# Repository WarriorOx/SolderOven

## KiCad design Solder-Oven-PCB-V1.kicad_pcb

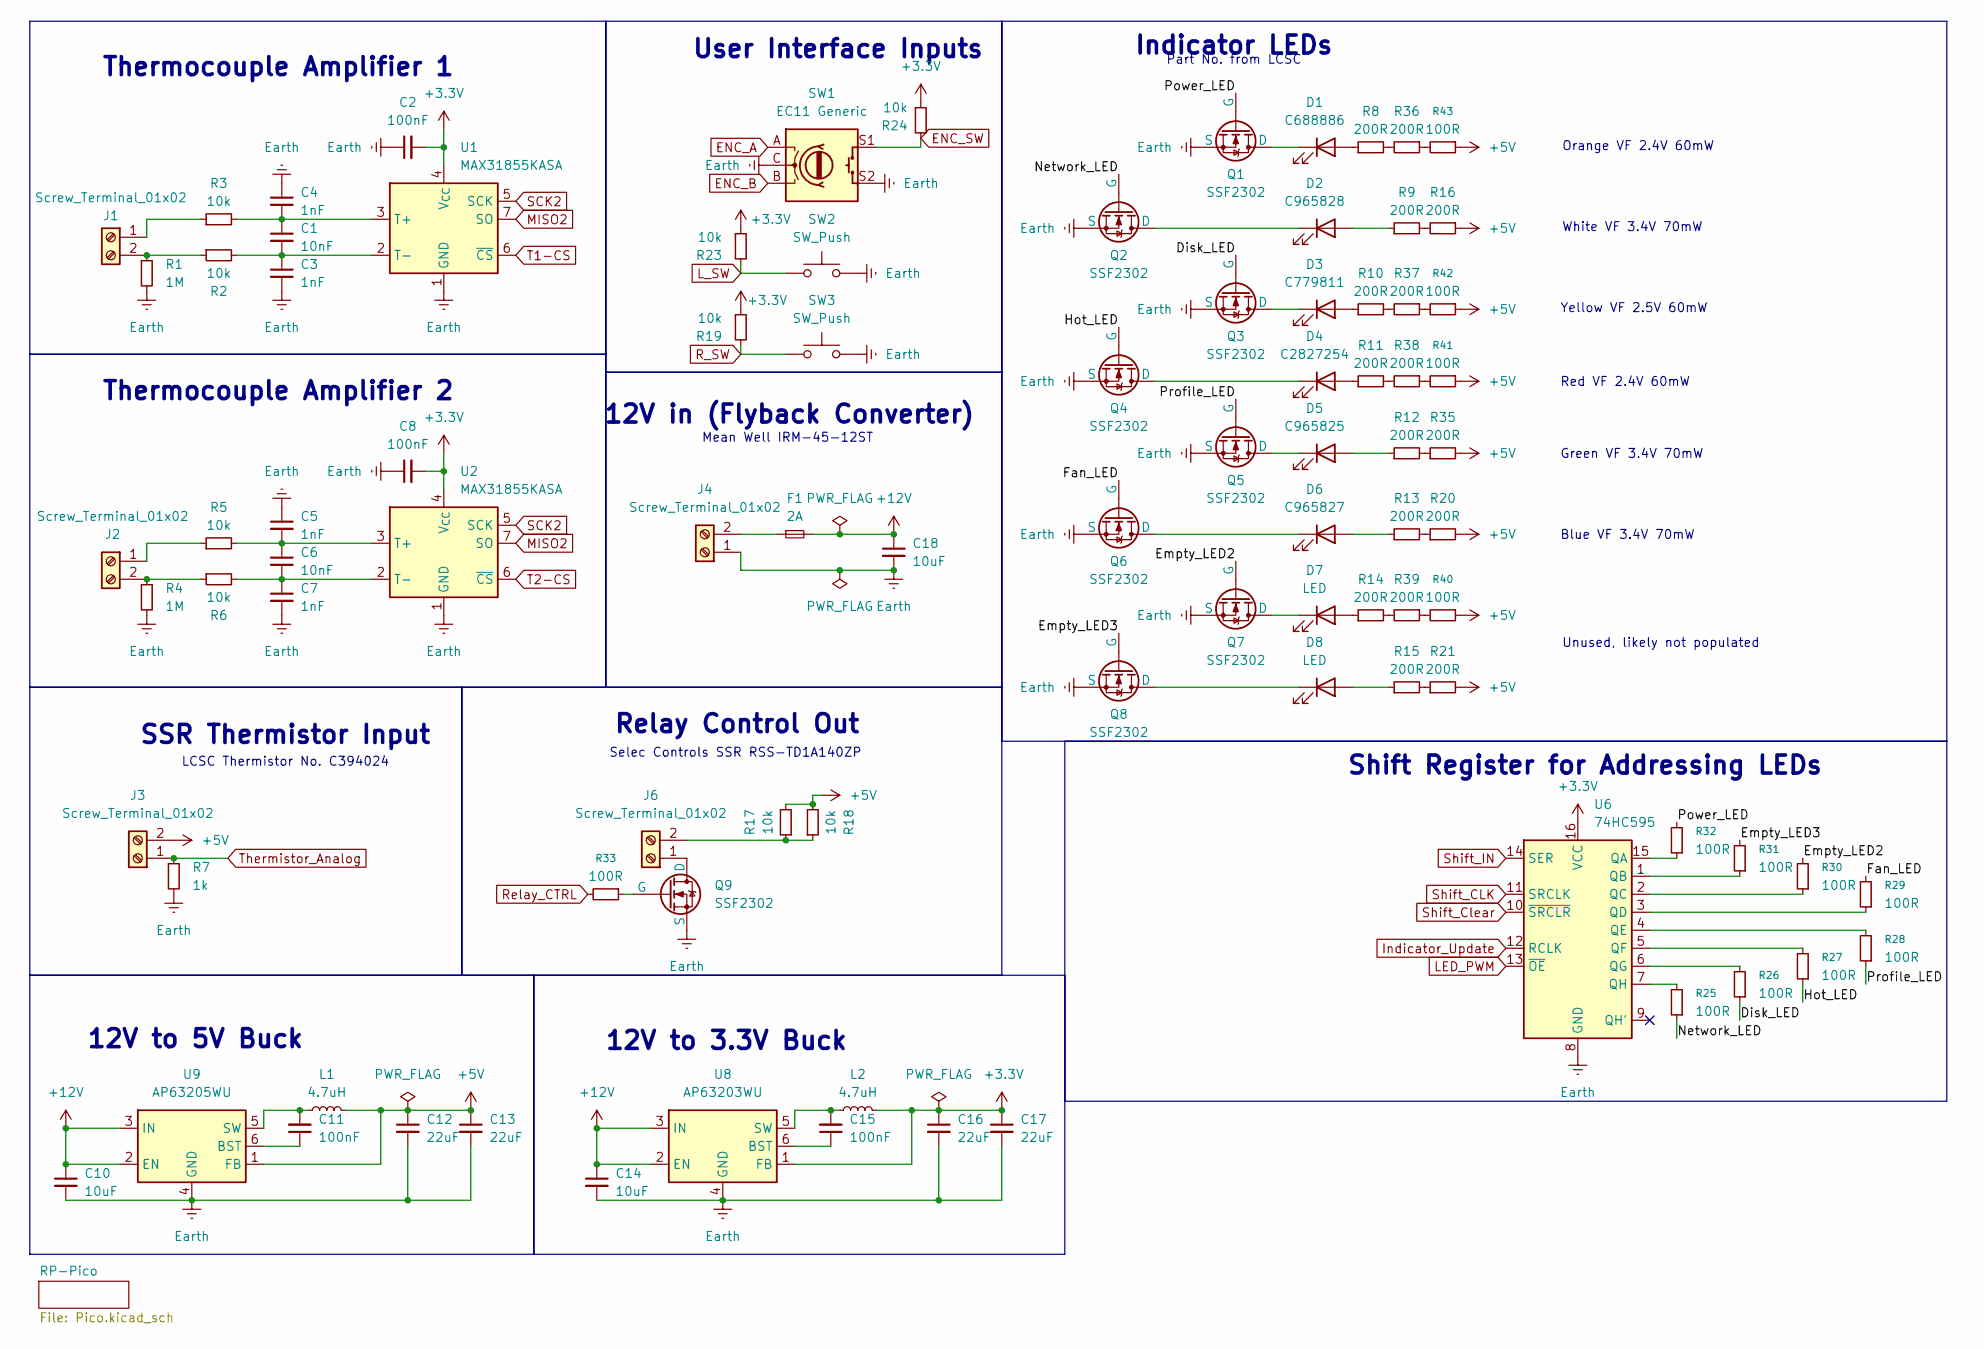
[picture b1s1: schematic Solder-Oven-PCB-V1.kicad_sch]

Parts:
C1, C6: 10nF; C_0603_1608Metric_Pad1.08x0.95mm_HandSolder
C2, C8, C11, C15: 100nF; C_0603_1608Metric_Pad1.08x0.95mm_HandSolder
C3, C4, C5, C7: 1nF; C_0603_1608Metric_Pad1.08x0.95mm_HandSolder
C10, C14, C18: 10uF; C_0603_1608Metric_Pad1.08x0.95mm_HandSolder
C12, C13, C16, C17: 22uF; C_0603_1608Metric_Pad1.08x0.95mm_HandSolder
D1: C688886; LED_1206_3216Metric_Pad1.42x1.75mm_HandSolder
D2: C965828; LED_1206_3216Metric_Pad1.42x1.75mm_HandSolder
D3: C779811; LED_1206_3216Metric_Pad1.42x1.75mm_HandSolder
D4: C2827254; LED_1206_3216Metric_Pad1.42x1.75mm_HandSolder
D5: C965825; LED_1206_3216Metric_Pad1.42x1.75mm_HandSolder
D6: C965827; LED_1206_3216Metric_Pad1.42x1.75mm_HandSolder
D7, D8: LED; LED_1206_3216Metric_Pad1.42x1.75mm_HandSolder
F1: 2A; Fuse_1812_4532Metric_Pad1.30x3.40mm_HandSolder
J1, J2, J3, J4, J6: Screw_Terminal_01x02; 1x2 5.08mm Screw Terminal
L1, L2: 4.7uH; LCSCC22463808
Q1, Q2, Q3, Q4, Q5, Q6, Q7, Q8, Q9: SSF2302; SOT-23-3
R1, R4: 1M; R_0603_1608Metric_Pad0.98x0.95mm_HandSolder
R2, R3, R5, R6, R17, R18, R19, R23, R24: 10k; R_0603_1608Metric_Pad0.98x0.95mm_HandSolder
R7: 1k; R_0603_1608Metric_Pad0.98x0.95mm_HandSolder
R8, R9, R10, R11, R12, R13, R14, R15, R16, R20, R21, R35, R36, R37, R38, R39: 200R; R_0603_1608Metric_Pad0.98x0.95mm_HandSolder
R25, R26, R27, R28, R29, R30, R31, R32, R33, R40, R41, R42, R43: 100R; R_0603_1608Metric_Pad0.98x0.95mm_HandSolder
SW1: EC11 Generic; RotaryEncoder_Alps_EC11E-Switch_Vertical_H20mm
SW2, SW3: SW_Push; MXOnly-1U-NoLED
U1, U2: MAX31855KASA; SOIC-8_3.9x4.9mm_P1.27mm
U6: 74HC595; SOP-16_3.9x9.9mm_P1.27mm
U8: AP63203WU; TSOT-23-6
U9: AP63205WU; TSOT-23-6

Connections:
+3.3V: C2.2, C8.2, C16.1, C17.1, L2.2, R19.1, R23.1, R24.1, U1.4 (V_{CC}), U2.4 (V_{CC}), U6.16 (VCC), U8.1 (FB); also elsewhere on the board
+5V: C12.1, C13.1, J3.2, L1.2, R16.1, R17.2, R18.2, R20.2, R21.2, R35.2, R40.1, R41.1, R42.1, R43.1, U9.1 (FB); also elsewhere on the board
+12V: C10.1, C14.1, C18.1, F1.2, U8.2 (EN), U8.3 (IN), U9.2 (EN), U9.3 (IN); also elsewhere on the board
/Disk_LED: Q3.2 (G), R26.1
/Empty_LED2: Q7.2 (G), R30.2
/Empty_LED3: Q8.2 (G), R31.2
/Fan_LED: Q6.2 (G), R29.2
/Hot_LED: Q4.2 (G), R27.1
/Network_LED: Q2.2 (G), R25.1
/Power_LED: Q1.2 (G), R32.2
/Profile_LED: Q5.2 (G), R28.1
ENC_A: SW1.A; also elsewhere on the board
ENC_B: SW1.B; also elsewhere on the board
ENC_SW: R24.2, SW1.S1; also elsewhere on the board
Earth: C2.1, C3.2, C4.1, C5.1, C7.2, C8.1, C10.2, C12.2, C13.2, C14.2, C16.2, C17.2, C18.2, J4.1, Q1.3 (S), Q2.3 (S), Q3.3 (S), Q4.3 (S), Q5.3 (S), Q6.3 (S), Q7.3 (S), Q8.3 (S), Q9.3 (S), R1.2, R4.2, R7.2, SW1.C, SW1.S2, SW2.2, SW3.2, U1.1 (GND), U2.1 (GND), U6.8 (GND), U8.4 (GND), U9.4 (GND); also elsewhere on the board
Indicator_Update: U6.12 (RCLK); also elsewhere on the board
LED_PWM: U6.13 (~OE); also elsewhere on the board
L_SW: R23.2, SW2.1; also elsewhere on the board
MISO2: U1.7 (SO), U2.7 (SO); also elsewhere on the board
unnamed: D1.2 (A), R8.1
unnamed: D1.1 (K), Q1.1 (D)
unnamed: D2.2 (A), R9.1
unnamed: D2.1 (K), Q2.1 (D)
unnamed: D3.2 (A), R10.1
unnamed: D3.1 (K), Q3.1 (D)
unnamed: D4.2 (A), R11.1
unnamed: D4.1 (K), Q4.1 (D)
unnamed: D5.2 (A), R12.1
unnamed: D5.1 (K), Q5.1 (D)
unnamed: D6.2 (A), R13.1
unnamed: D6.1 (K), Q6.1 (D)
unnamed: D7.2 (A), R14.1
unnamed: D7.1 (K), Q7.1 (D)
unnamed: D8.2 (A), R15.1
unnamed: D8.1 (K), Q8.1 (D)
unnamed: J1.1, R3.1
unnamed: J1.2, R1.1, R2.1
unnamed: J2.1, R5.1
unnamed: J2.2, R4.1, R6.1
unnamed: F1.1, J4.2
unnamed: J6.1, Q9.1 (D)
unnamed: J6.2, R17.1, R18.1
unnamed: Q9.2 (G), R33.1
unnamed: R10.2, R37.2
unnamed: R11.2, R38.2
unnamed: R12.2, R35.1
unnamed: R13.2, R20.1
unnamed: R14.2, R39.2
unnamed: R15.2, R21.1
unnamed: R9.2, R16.2
unnamed: R36.1, R43.2
unnamed: R8.2, R36.2
unnamed: R37.1, R42.2
unnamed: R38.1, R41.2
unnamed: R39.1, R40.2
unnamed: C1.1, C4.2, R3.2, U1.3 (T+)
unnamed: C1.2, C3.1, R2.2, U1.2 (T-)
unnamed: C5.2, C6.1, R5.2, U2.3 (T+)
unnamed: C6.2, C7.1, R6.2, U2.2 (T-)
unnamed: R32.1, U6.15 (QA)
unnamed: R31.1, U6.1 (QB)
unnamed: R30.1, U6.2 (QC)
unnamed: R29.1, U6.3 (QD)
unnamed: R28.2, U6.4 (QE)
unnamed: R27.2, U6.5 (QF)
unnamed: R26.2, U6.6 (QG)
unnamed: R25.2, U6.7 (QH)
unnamed: C15.1, U8.6 (BST)
unnamed: C15.2, L2.1, U8.5 (SW)
unnamed: C11.1, U9.6 (BST)
unnamed: C11.2, L1.1, U9.5 (SW)
R_SW: R19.2, SW3.1; also elsewhere on the board
Relay_CTRL: R33.2; also elsewhere on the board
SCK2: U1.5 (SCK), U2.5 (SCK); also elsewhere on the board
Shift_CLK: U6.11 (SRCLK); also elsewhere on the board
Shift_Clear: U6.10 (~SRCLR); also elsewhere on the board
Shift_IN: U6.14 (SER); also elsewhere on the board
T1-CS: U1.6 (~CS); also elsewhere on the board
T2-CS: U2.6 (~CS); also elsewhere on the board
Thermistor_Analog: J3.1, R7.1; also elsewhere on the board

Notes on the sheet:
Thermocouple Amplifier 1
Yellow VF 2.5V 60mW
Orange VF 2.4V 60mW
Part No. from LCSC
User Interface Inputs
White VF 3.4V 70mW
Thermocouple Amplifier 2
Mean Well IRM-45-12ST
12V to 3.3V Buck
Blue VF 3.4V 70mW
LCSC Thermistor No. C394024
Green VF 3.4V 70mW
Shift Register for Addressing LEDs
SSR Thermistor Input
Red VF 2.4V 60mW
Unused, likely not populated
12V to 5V Buck
Relay Control Out
Indicator LEDs
12V in (Flyback Converter)
Selec Controls SSR RSS-TD1A140ZP

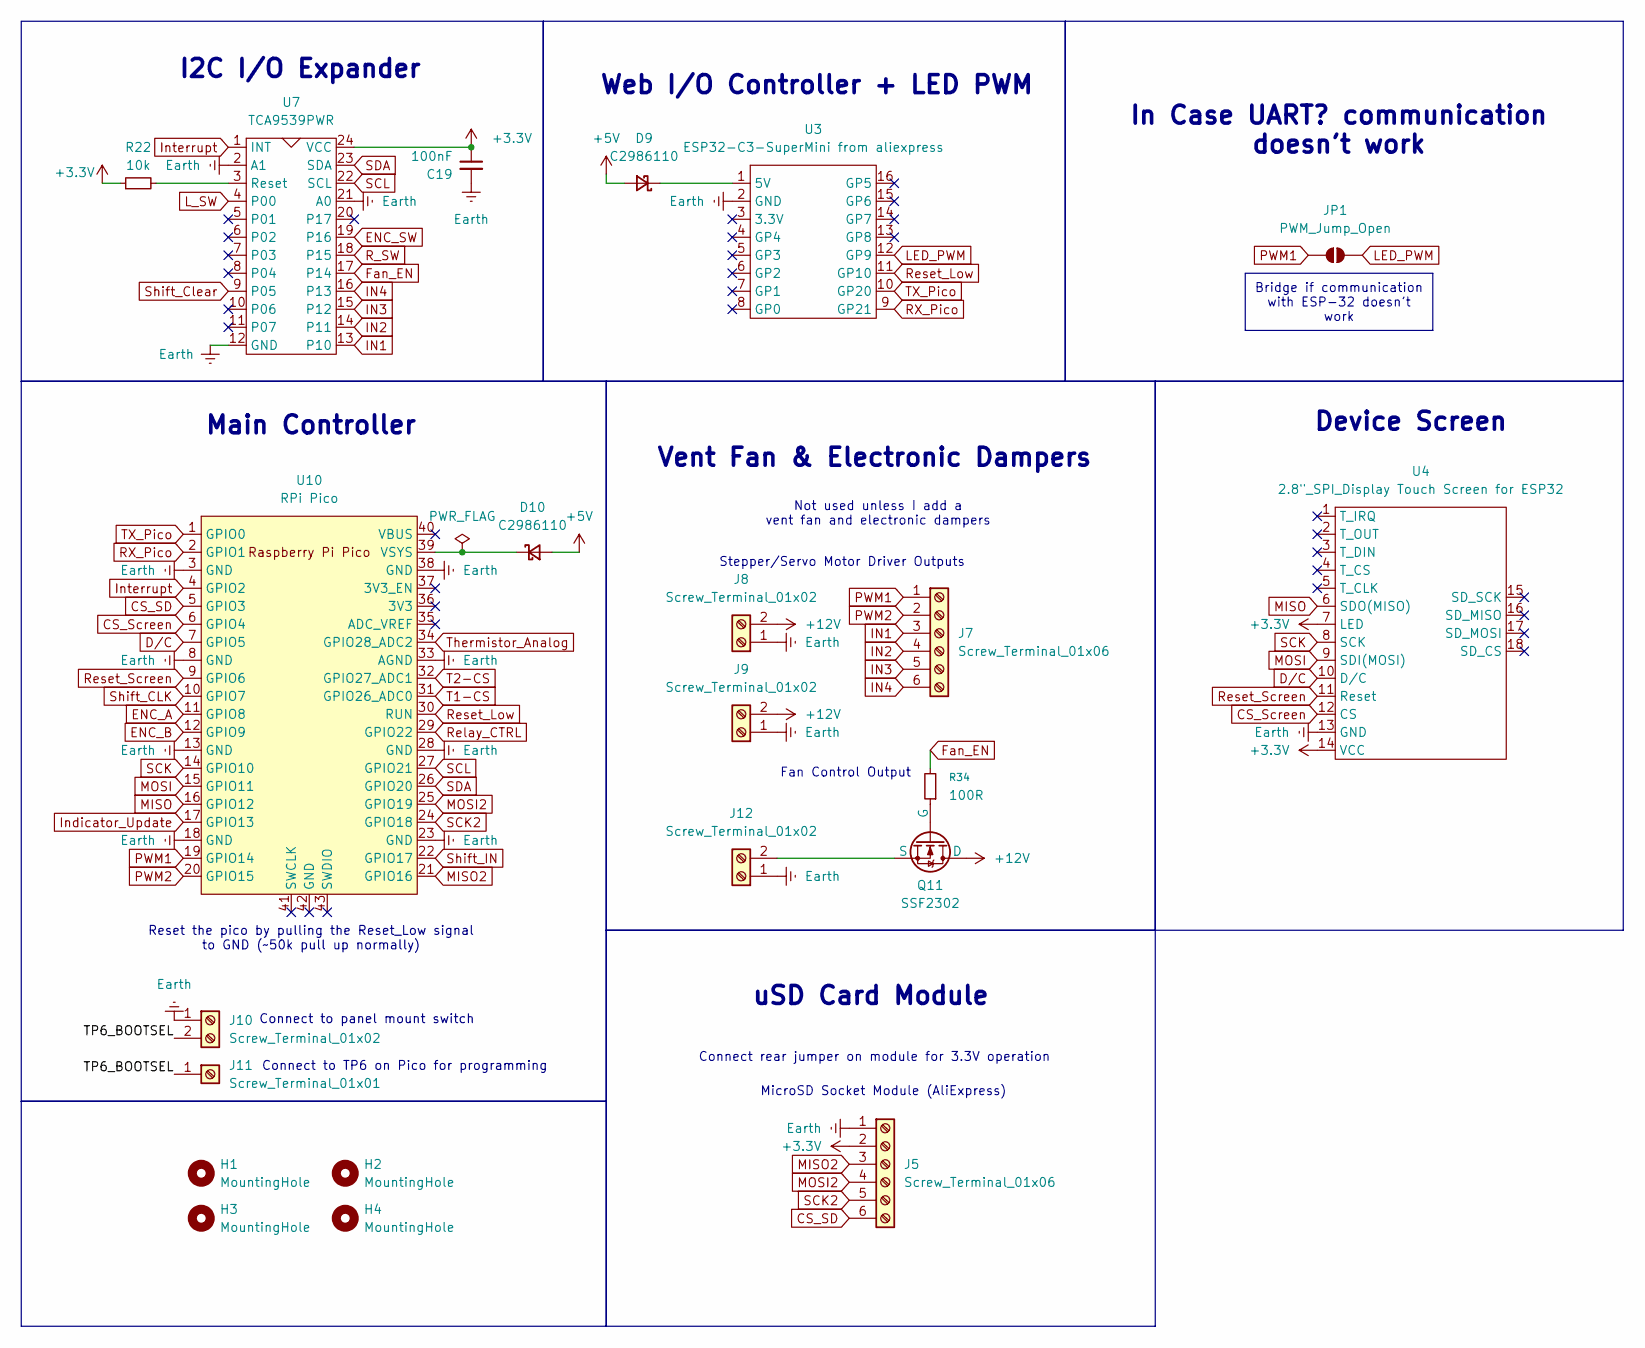
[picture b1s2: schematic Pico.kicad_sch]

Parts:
C19: 100nF; C_0603_1608Metric_Pad1.08x0.95mm_HandSolder
D9, D10: C2986110; D_SMA_Handsoldering
H1, H2, H3, H4: MountingHole; MountingHole_4mm_Pad
J5, J7: Screw_Terminal_01x06; 1x6 2.54mm Screw Terminal
J8, J9, J10, J12: Screw_Terminal_01x02; 1x2 5.08mm Screw Terminal
J11: Screw_Terminal_01x01; PinSocket_1x01_P2.54mm_Vertical
JP1: PWM_Jump_Open; SolderJumper-2_P1.3mm_Open_TrianglePad1.0x1.5mm
Q11: SSF2302; SOT-23-3
R22: 10k; R_0603_1608Metric_Pad0.98x0.95mm_HandSolder
R34: 100R; R_0603_1608Metric_Pad0.98x0.95mm_HandSolder
U3: ESP32-C3-SuperMini from aliexpress; ESP32-C3_SUPERMINI
U4: 2.8"_SPI_Display Touch Screen for ESP32; 2.8in TFT Display
U7: TCA9539PWR; TSSOP-24_4.4x7.8mm_P0.65mm
U10: RPi Pico; RPi_Pico_SMD_TH

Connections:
+3.3V: C19.1, J5.2, R22.1, U4.7 (LED), U4.14 (VCC), U7.24 (VCC); also elsewhere on the board
+5V: D9.2 (A), D10.2 (A); also elsewhere on the board
+12V: J8.2, J9.2, Q11.1 (D); also elsewhere on the board
/RP-Pico/TP6_BOOTSEL: J10.2, J11.1
CS_SD: J5.6, U10.5 (GPIO3)
CS_Screen: U4.12 (CS), U10.6 (GPIO4)
D/C: U4.10 (D/C), U10.7 (GPIO5)
ENC_A: U10.11 (GPIO8); also elsewhere on the board
ENC_B: U10.12 (GPIO9); also elsewhere on the board
ENC_SW: U7.19 (P16); also elsewhere on the board
Earth: C19.2, J5.1, J8.1, J9.1, J10.1, J12.1, U3.2 (GND), U4.13 (GND), U7.2 (A1), U7.12 (GND), U7.21 (A0), U10.3 (GND), U10.8 (GND), U10.13 (GND), U10.18 (GND), U10.23 (GND), U10.28 (GND), U10.33 (AGND), U10.38 (GND); also elsewhere on the board
Fan_EN: R34.2, U7.17 (P14)
IN1: J7.3, U7.13 (P10)
IN2: J7.4, U7.14 (P11)
IN3: J7.5, U7.15 (P12)
IN4: J7.6, U7.16 (P13)
Indicator_Update: U10.17 (GPIO13); also elsewhere on the board
Interrupt: U7.1 (INT), U10.4 (GPIO2)
LED_PWM: JP1.2 (B), U3.12 (GP9); also elsewhere on the board
L_SW: U7.4 (P00); also elsewhere on the board
MISO: U4.6 (SDO(MISO)), U10.16 (GPIO12)
MISO2: J5.3, U10.21 (GPIO16); also elsewhere on the board
MOSI: U4.9 (SDI(MOSI)), U10.15 (GPIO11)
MOSI2: J5.4, U10.25 (GPIO19)
unnamed: D9.1 (K), U3.1 (5V)
unnamed: D10.1 (K), U10.39 (VSYS)
unnamed: J12.2, Q11.3 (S)
unnamed: Q11.2 (G), R34.1
unnamed: R22.2, U7.3 (Reset)
PWM1: J7.1, JP1.1 (A), U10.19 (GPIO14)
PWM2: J7.2, U10.20 (GPIO15)
RX_Pico: U3.9 (GP21), U10.2 (GPIO1)
R_SW: U7.18 (P15); also elsewhere on the board
Relay_CTRL: U10.29 (GPIO22); also elsewhere on the board
Reset_Low: U3.11 (GP10), U10.30 (RUN)
Reset_Screen: U4.11 (Reset), U10.9 (GPIO6)
SCK: U4.8 (SCK), U10.14 (GPIO10)
SCK2: J5.5, U10.24 (GPIO18); also elsewhere on the board
SCL: U7.22 (SCL), U10.27 (GPIO21)
SDA: U7.23 (SDA), U10.26 (GPIO20)
Shift_CLK: U10.10 (GPIO7); also elsewhere on the board
Shift_Clear: U7.9 (P05); also elsewhere on the board
Shift_IN: U10.22 (GPIO17); also elsewhere on the board
T1-CS: U10.31 (GPIO26_ADC0); also elsewhere on the board
T2-CS: U10.32 (GPIO27_ADC1); also elsewhere on the board
TX_Pico: U3.10 (GP20), U10.1 (GPIO0)
Thermistor_Analog: U10.34 (GPIO28_ADC2); also elsewhere on the board

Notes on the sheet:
Main Controller
I2C I/O Expander
Connect rear jumper on module for 3.3V operation
Device Screen
uSD Card Module
MicroSD Socket Module (AliExpress)
In Case UART? communication doesn't work
Not used unless I add a vent fan and electronic dampers
Fan Control Output
Web I/O Controller + LED PWM
Reset the pico by pulling the Reset_Low signal to GND (~50k pull up normally)
Connect to panel mount switch
Vent Fan & Electronic Dampers
Connect to TP6 on Pico for programming
Stepper/Servo Motor Driver Outputs
Bridge if communication with ESP-32 doesn't work

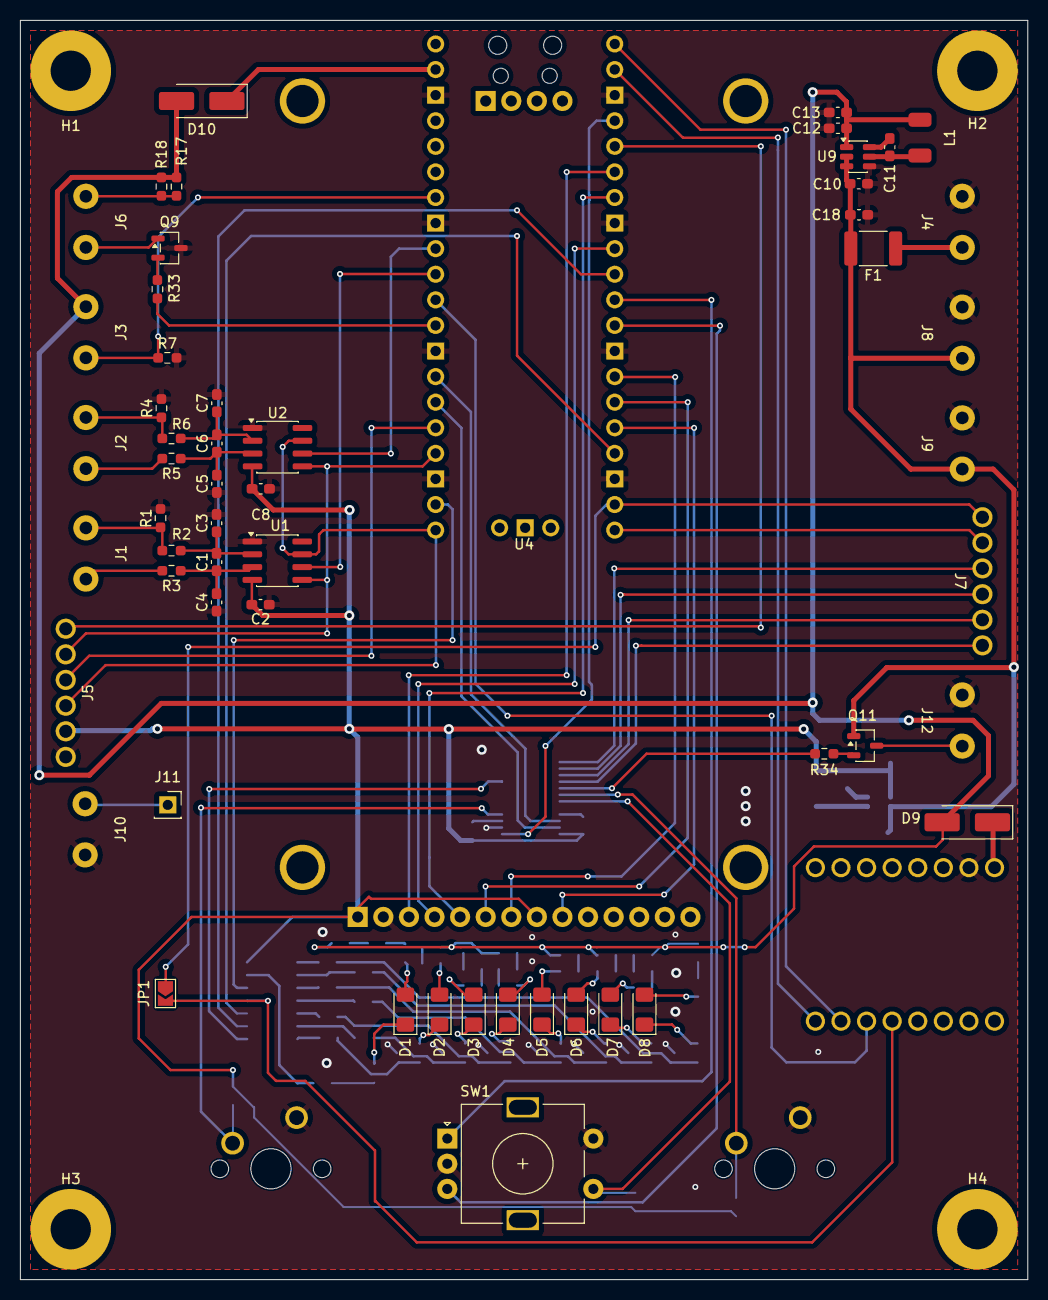
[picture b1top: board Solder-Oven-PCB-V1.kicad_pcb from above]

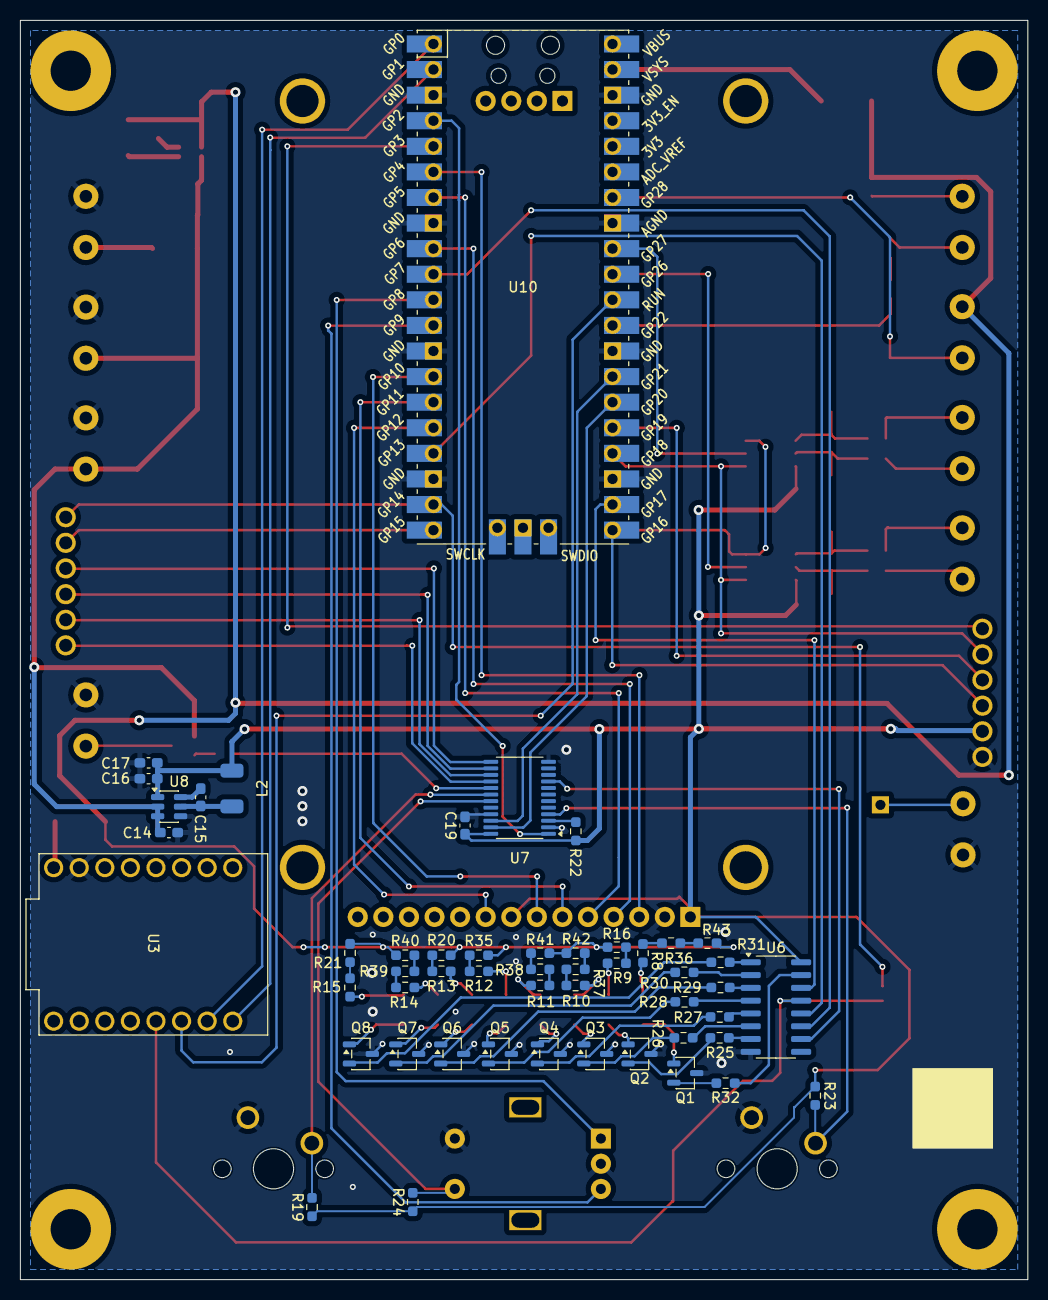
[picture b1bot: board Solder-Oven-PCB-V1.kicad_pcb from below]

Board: 2 copper layers, 100.0 x 125.0 mm, 113 parts (51 on the bottom side), 107 nets.
